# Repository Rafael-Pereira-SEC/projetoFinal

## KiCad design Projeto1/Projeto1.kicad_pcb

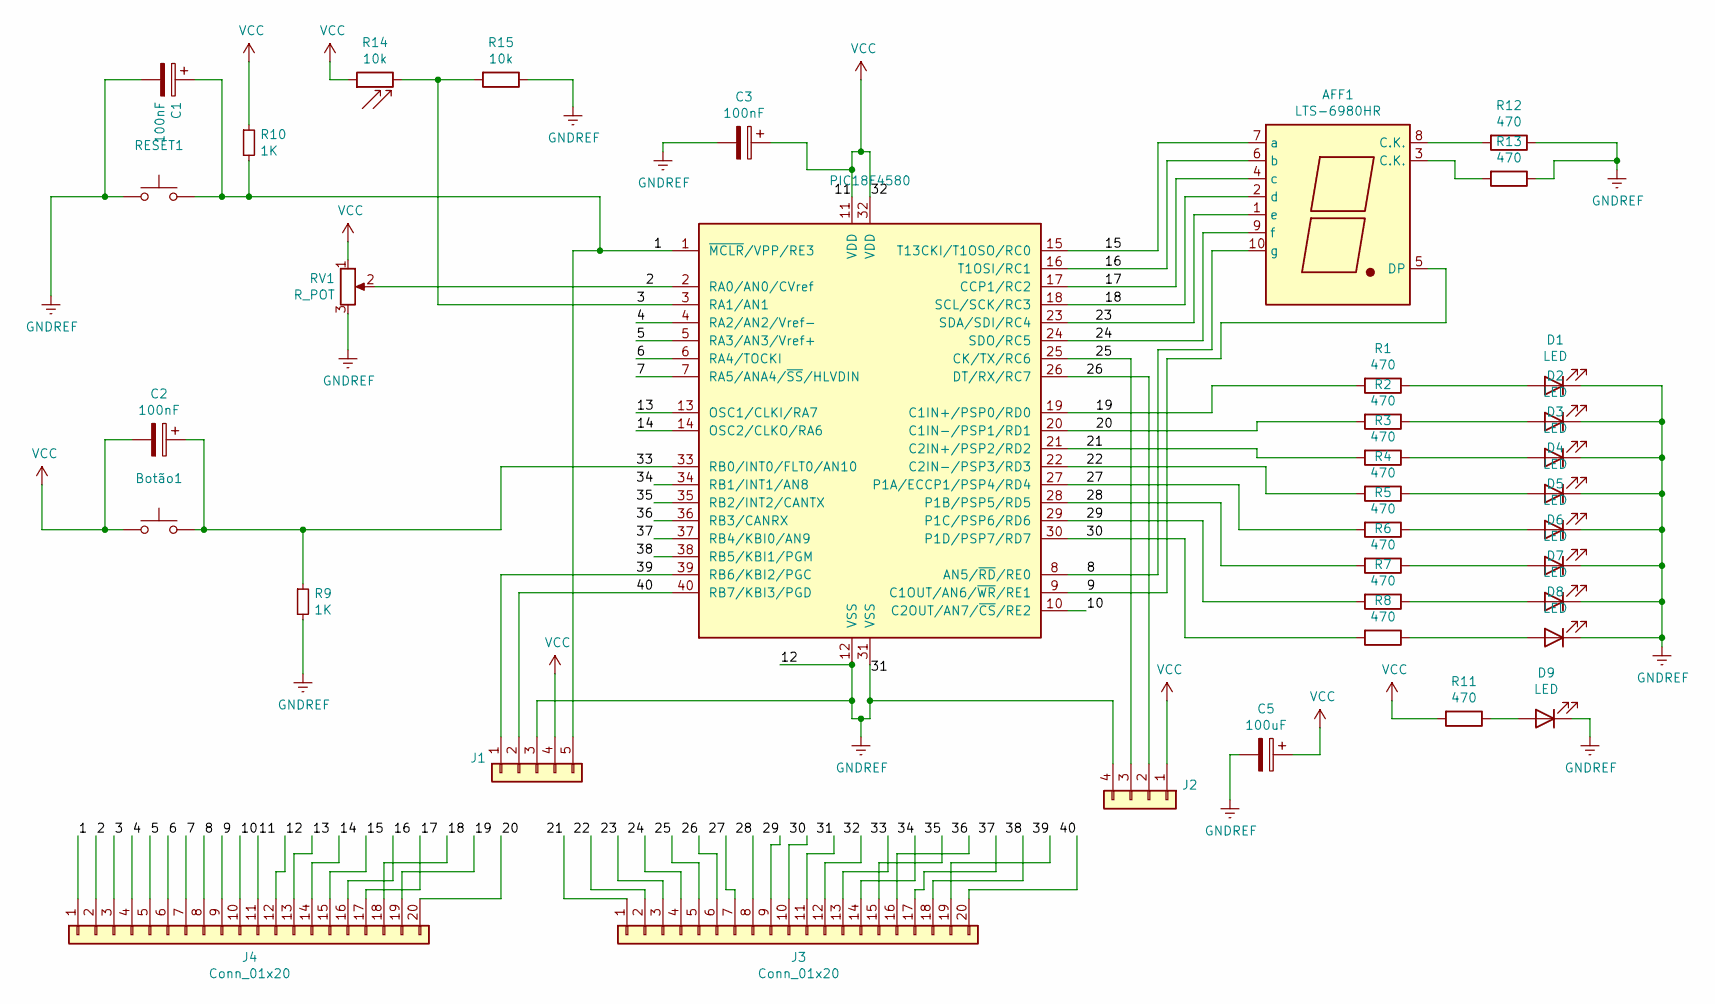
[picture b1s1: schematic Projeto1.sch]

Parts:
AFF1: LTS-6980HR; 7SegmentLED_LTS6760_LTS6780
Botão1: SW_Push; SW_PUSH_6mm_H4.3mm
C1, C2, C3: 100nF; C_Disc_D6.0mm_W2.5mm_P5.00mm
C5: 100uF; C_Radial_D6.3mm_H5.0mm_P2.50mm
D1, D2, D3, D4, D5, D6, D7, D8, D9: LED; LED_D3.0mm
J1: Conn_01x05; PinHeader_1x05_P2.54mm_Horizontal
J2: Conn_01x04; PinSocket_1x04_P2.54mm_Horizontal
J3, J4: Conn_01x20; PinHeader_1x20_P2.54mm_Vertical
PIC18F4580: PIC18F4580-IP; DIP-40_W15.24mm
R1, R2, R3, R4, R5, R6, R7, R8, R11, R12, R13: 470; R_Axial_DIN0207_L6.3mm_D2.5mm_P7.62mm_Horizontal
R9, R10: 1K; R_Axial_DIN0207_L6.3mm_D2.5mm_P7.62mm_Horizontal
R14: 10k; R_LDR_7x6mm_P5.1mm_Vertical
R15: 10k; R_Axial_DIN0207_L6.3mm_D2.5mm_P7.62mm_Horizontal
RESET1: SW_Push; SW_PUSH_6mm_H5mm
RV1: R_POT; Potentiometer_Vishay_T73YP_Vertical

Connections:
/1: C1.1, J1.5, J4.1, PIC18F4580.1 (~MCLR~/VPP/RE3), R10.2, RESET1.2
/2: J4.2, PIC18F4580.2 (RA0/AN0/CVref), RV1.2
/3: J4.3, PIC18F4580.3 (RA1/AN1), R14.2, R15.2
/4: J4.4, PIC18F4580.4 (RA2/AN2/Vref-)
/5: J4.5, PIC18F4580.5 (RA3/AN3/Vref+)
/6: J4.6, PIC18F4580.6 (RA4/TOCKI)
/7: J4.7, PIC18F4580.7 (RA5/ANA4/~SS~/HLVDIN)
/8: AFF1.10 (g), J4.8, PIC18F4580.8 (AN5/~RD~/RE0)
/9: AFF1.5 (DP), J4.9, PIC18F4580.9 (C1OUT/AN6/~WR~/RE1)
/10: J4.10, PIC18F4580.10 (C2OUT/AN7/~CS~/RE2)
/13: J4.13, PIC18F4580.13 (OSC1/CLKI/RA7)
/14: J4.14, PIC18F4580.14 (OSC2/CLKO/RA6)
/15: AFF1.7 (a), J4.15, PIC18F4580.15 (T13CKI/T1OSO/RC0)
/16: AFF1.6 (b), J4.16, PIC18F4580.16 (T1OSI/RC1)
/17: AFF1.4 (c), J4.17, PIC18F4580.17 (CCP1/RC2)
/18: AFF1.2 (d), J4.18, PIC18F4580.18 (SCL/SCK/RC3)
/19: J4.19, PIC18F4580.19 (C1IN+/PSP0/RD0), R1.2
/20: J4.20, PIC18F4580.20 (C1IN-/PSP1/RD1), R2.2
/21: J3.1, PIC18F4580.21 (C2IN+/PSP2/RD2), R3.2
/22: J3.2, PIC18F4580.22 (C2IN-/PSP3/RD3), R4.2
/23: AFF1.1 (e), J3.3, PIC18F4580.23 (SDA/SDI/RC4)
/24: AFF1.9 (f), J3.4, PIC18F4580.24 (SDO/RC5)
/25: J2.3, J3.5, PIC18F4580.25 (CK/TX/RC6)
/26: J2.2, J3.6, PIC18F4580.26 (DT/RX/RC7)
/27: J3.7, PIC18F4580.27 (P1A/ECCP1/PSP4/RD4), R5.2
/28: J3.8, PIC18F4580.28 (P1B/PSP5/RD5), R6.2
/29: J3.9, PIC18F4580.29 (P1C/PSP6/RD6), R7.2
/30: J3.10, PIC18F4580.30 (P1D/PSP7/RD7), R8.2
/33: Botão1.2, C2.1, J3.13, PIC18F4580.33 (RB0/INT0/FLT0/AN10), R9.1
/34: J3.14, PIC18F4580.34 (RB1/INT1/AN8)
/35: J3.15, PIC18F4580.35 (RB2/INT2/CANTX)
/36: J3.16, PIC18F4580.36 (RB3/CANRX)
/37: J3.17, PIC18F4580.37 (RB4/KBI0/AN9)
/38: J3.18, PIC18F4580.38 (RB5/KBI1/PGM)
/39: J1.1, J3.19, PIC18F4580.39 (RB6/KBI2/PGC)
/40: J1.2, J3.20, PIC18F4580.40 (RB7/KBI3/PGD)
GNDREF: C1.2, C3.2, C5.2, D1.1 (K), D2.1 (K), D3.1 (K), D4.1 (K), D5.1 (K), D6.1 (K), D7.1 (K), D8.1 (K), D9.1 (K), J1.3, J2.4, J3.11, J4.12, PIC18F4580.12 (VSS), PIC18F4580.31 (VSS), R9.2, R12.1, R13.1, R15.1, RESET1.1, RV1.3
unnamed: AFF1.3 (C.K.), R13.2
unnamed: AFF1.8 (C.K.), R12.2
unnamed: D1.2 (A), R1.1
unnamed: D2.2 (A), R2.1
unnamed: D3.2 (A), R3.1
unnamed: D4.2 (A), R4.1
unnamed: D5.2 (A), R5.1
unnamed: D6.2 (A), R6.1
unnamed: D7.2 (A), R7.1
unnamed: D8.2 (A), R8.1
unnamed: D9.2 (A), R11.1
VCC: Botão1.1, C2.2, C3.1, C5.1, J1.4, J2.1, J3.12, J4.11, PIC18F4580.11 (VDD), PIC18F4580.32 (VDD), R10.1, R11.2, R14.1, RV1.1

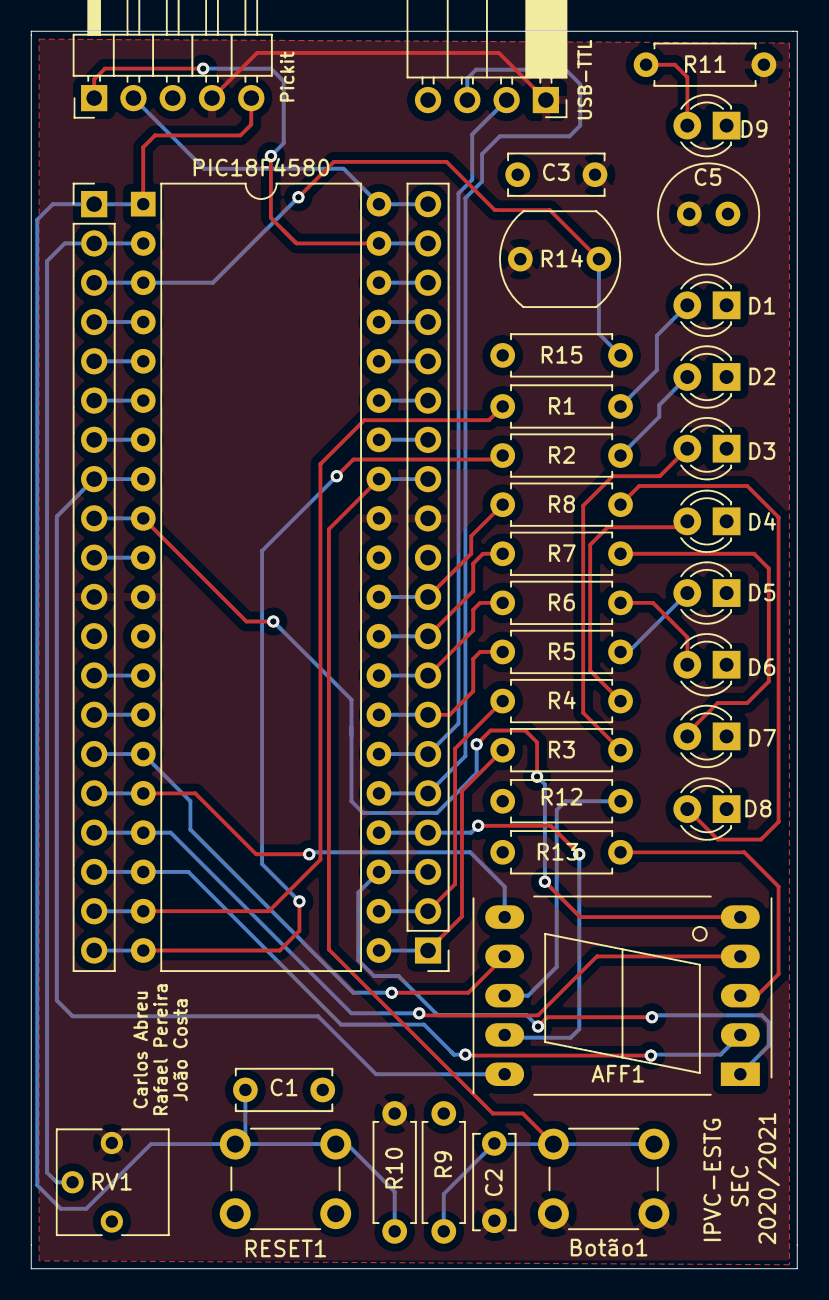
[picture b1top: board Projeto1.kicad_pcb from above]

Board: 2 copper layers, 49.5 x 80.0 mm, 37 parts (0 on the bottom side), 49 nets.

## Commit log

2021-01-24 versão1
